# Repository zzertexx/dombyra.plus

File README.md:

# Dombyra Plus
Simple device to teach playing on Dombyra!

## Description
Have you ever wanted to learn playing Dombyra at home?
If yes, then you absolutely looked resources to learn, and what you found was some videos that shows you how they play, while you need to everytime find out which notes is being pressed.

I had exact same problem, so I built this!

This device is solution for it. First hardware addon for Dombyra.

Using bunch of SK6812 LEDs on Dombyra's neck, it will show you which notes need to be pressed right now and after.
By ESP32 and INMP441 mic, it will be controlled by local Website to choose notes and continue showing notes.

## Features
* Wi-Fi website to choose kuis
* 18 LEDs per string with two color mod for Up/Down play
* Battery charge system for autonomuos play
* Comfortable case to play
* Volume spike detector to continue play

## Firmware
* Firmware was written on Arduino IDE
* Currently it has Erkem-Ai
* Needed libraries: FastLED.h, i2s.h(core), WiFi.h(core), WebServer.h(core)

## Attachment
To make sure cases won't move, I added attachment legs for **LED case** and also usage of nylon tape for **microphone case** so you can remove device whenever you want

## How to actually use it?
1) Assemble PCB into Case
2) Use nylon to attach microphone case
3) Compile code into ESP32
4) Place PCBs on dombyra and connect both using **4-pin JST XH2.54** and specialized pins
5) Charge battery and start it
6) Connect to ESP32's Wi-Fi and enter http://192.168.4.1
7) Choose the kui that you wanna learn and enjoy the process!

## Bill of Materials

| Component | Quantity |
|---|---|
| ESP32 DevKit v1 | 1 |
| SK6812 LEDs | 38 |
| INMP441 module | 1 |
| Li-Po Battery + 2 pin header 2mm | 1 |
| USB-C Receptacle only 6 pin | 1 |
| TP4056 module | 1 |
| MT3608 module | 1 |
| M2 screws | 14 |
| M3 screws | 4 |
| 4 pin Connector Sockets - Angled | 1 |
| 4 pin Connector Sockets - Vertical | 1 |
| NTC 10k | 1 |
| Unpolarized capacitors(THT) 10uF & 22uF | 2 each |
| Inductor 4.7uH | 1 |
| Diode | 2 LED and 1 Schottky |
| Resistors | 110k; 15k; 330 x2; 68k; 2.4k; 1k; 0.4; 5k1 x2 |
| 4-pin JST XH2.54 | 1 |
| Nylon Tape | 1 |

## PCB & Schematics
Designed on KiCad 10.0

It consists of 2 PCBs. One on neck for LEDs and second one for Battery, Microphone and MCU. They are connected using 4-pin JST wires for GND, 5V and 2 data channels. 

## Images of cases

## Demo 

https://youtu.be/3Eh5J_6kmjc

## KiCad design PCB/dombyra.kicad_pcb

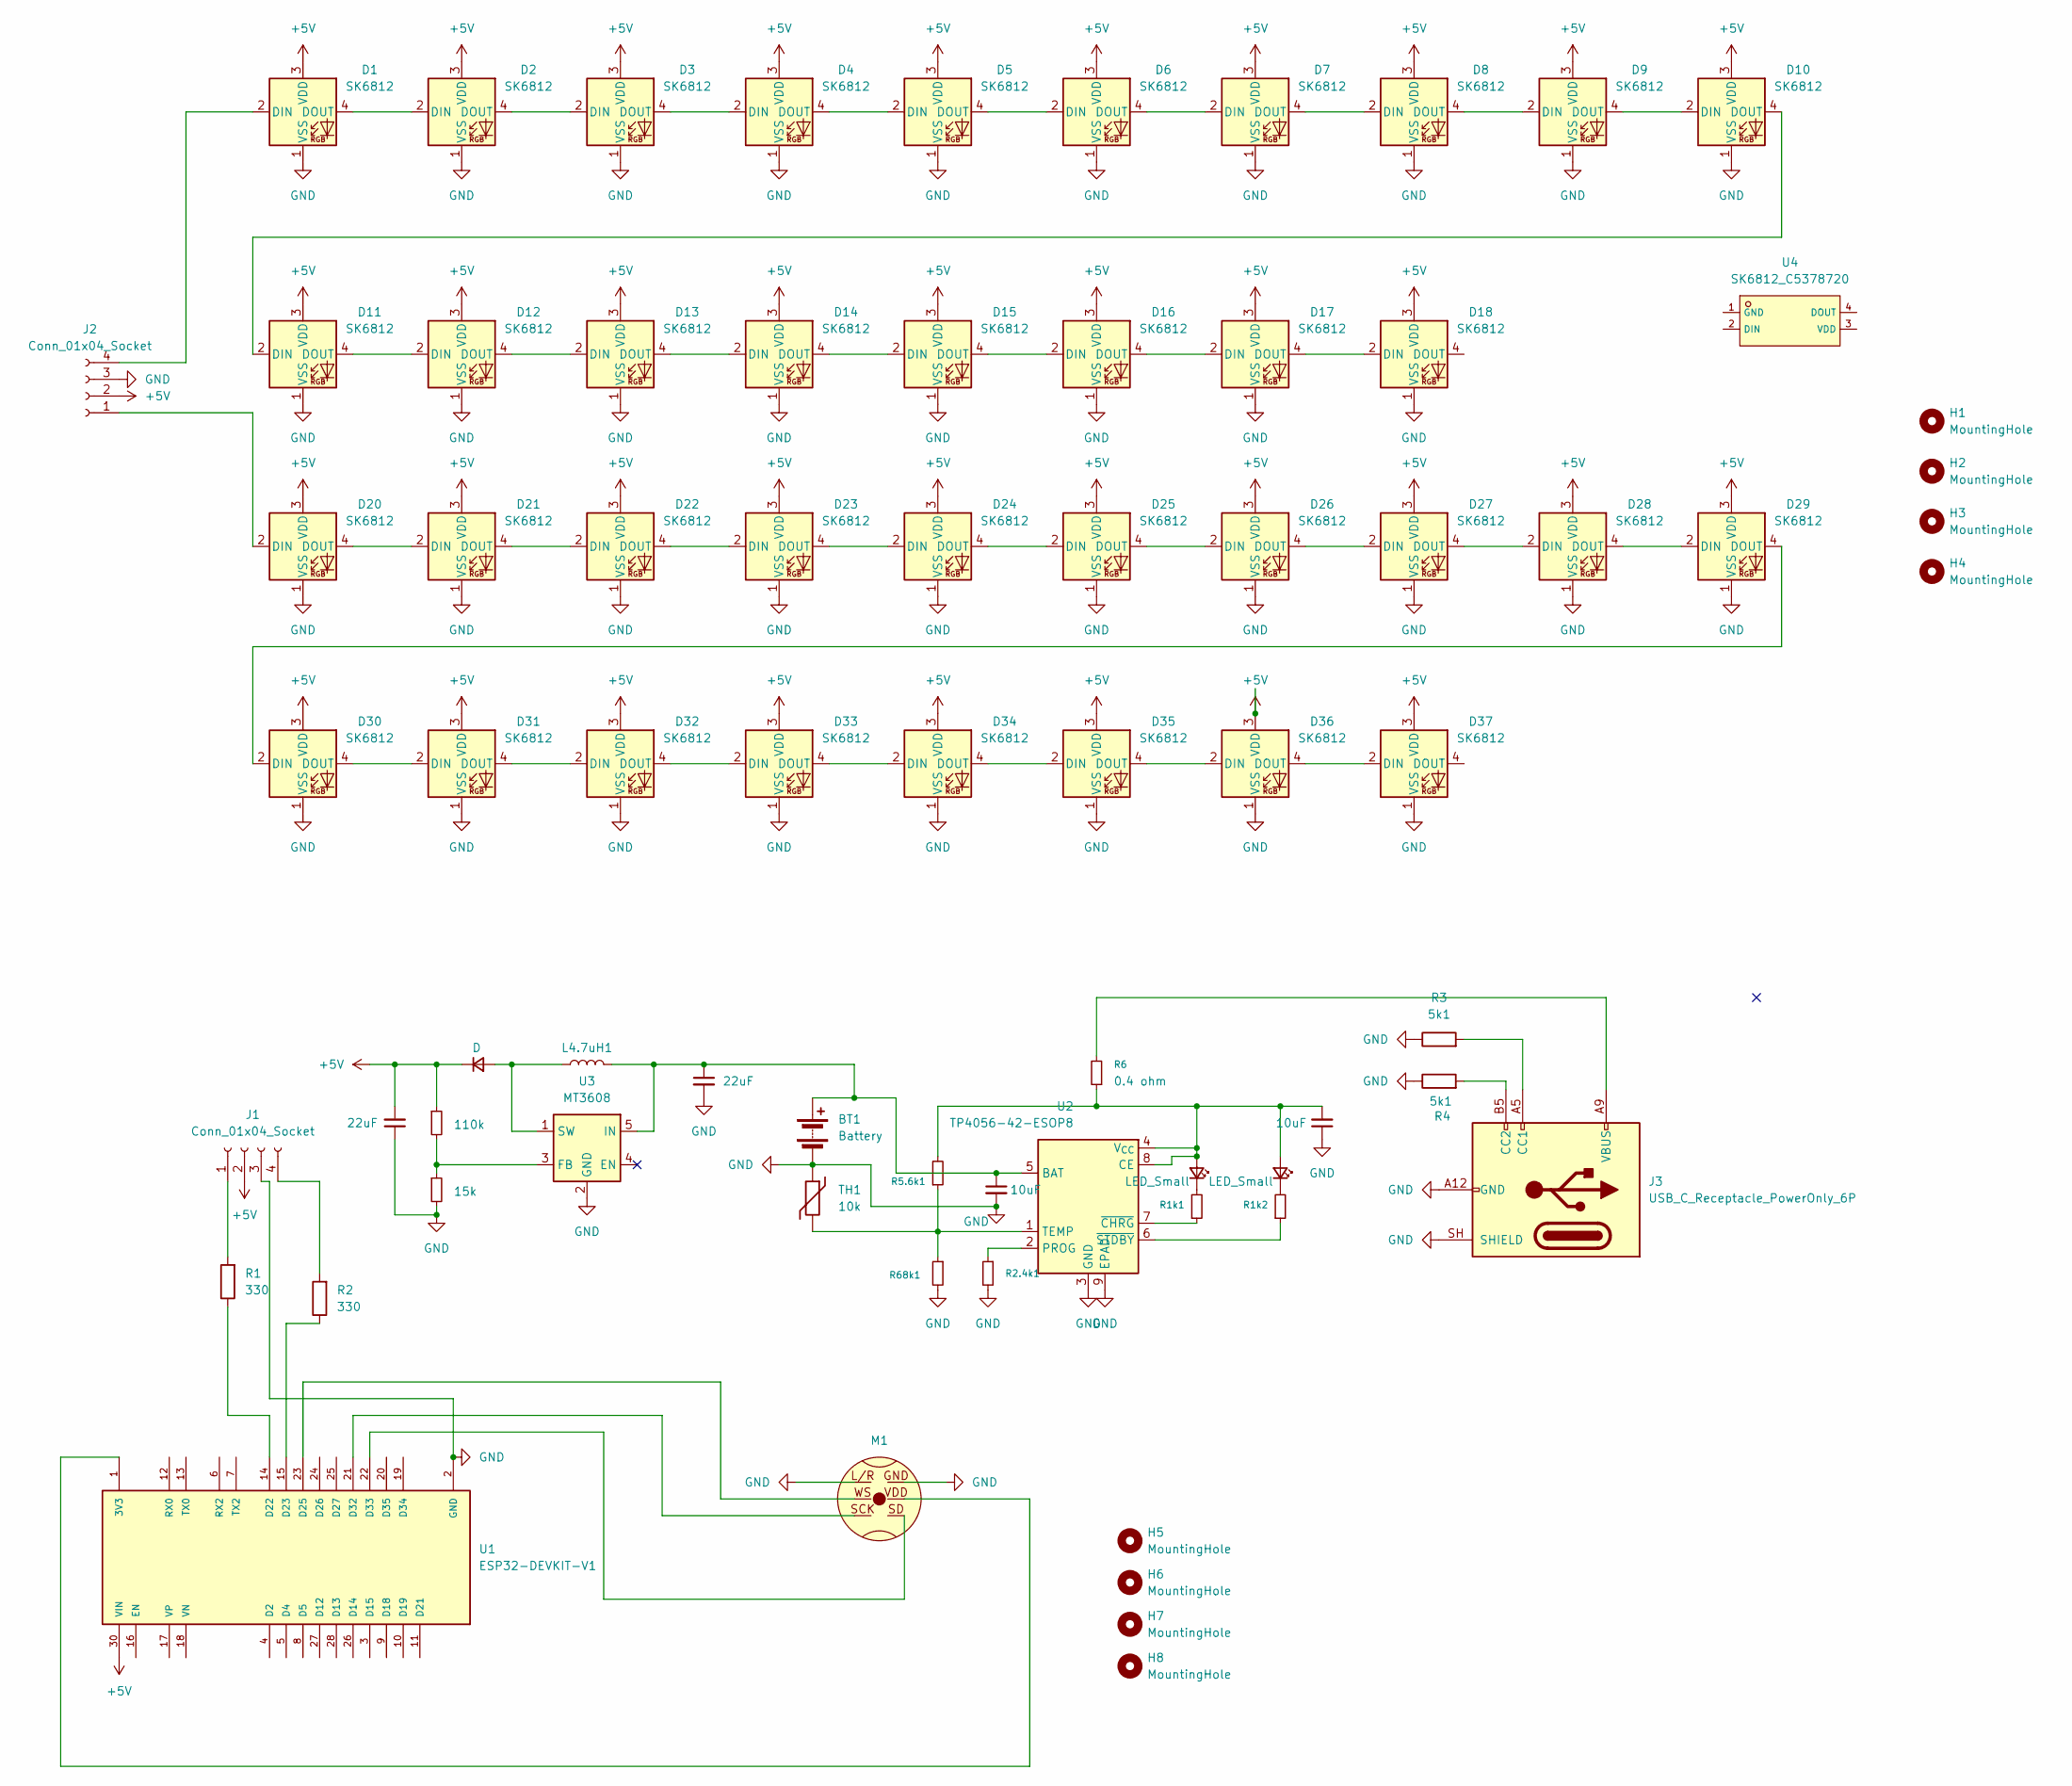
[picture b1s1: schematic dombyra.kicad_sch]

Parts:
BT1: Battery; PinHeader_1x02_P2.54mm_Vertical
C1, C2: 10uF; C_0805_2012Metric
C3, C4: 22uF; C_1206_3216Metric
D1, D2, D3, D4, D5, D6, D7, D8, D9, D10, D11, D12, D13, D14, D15, D16, D17, D18, D20, D21, D22, D23, D24, D25, D26, D27, D28, D29, D30, D31, D32, D33, D34, D35, D36, D37: SK6812; LED_SK6812_PLCC4_5.0x5.0mm_P3.2mm
D39: LED_Small; LED_D3.0mm
D40: LED_Small; LED_D5.0mm
D41: D; SMA_L4.3-W2.6-LS5.2-RD
H1, H2, H3, H4: MountingHole; MountingHole_3.2mm_M3
H5, H6, H7, H8: MountingHole; MountingHole_2.2mm_M2
J1: Conn_01x04_Socket; PinHeader_1x04_P2.54mm_Vertical_SMD_Pin1Left
J2: Conn_01x04_Socket; PinHeader_1x04_P2.54mm_Horizontal
J3: USB_C_Receptacle_PowerOnly_6P; USB_C_Receptacle_GCT_USB4135-GF-A_6P_TopMnt_Horizontal
L4.7uH1: L; L_1812_4532Metric
M1: INMP441
R1, R2: 330; R_0402_1005Metric
R1k1, R1k2: R_Small; R_0805_2012Metric
R2.4k1: R_Small; R_Axial_DIN0204_L3.6mm_D1.6mm_P1.90mm_Vertical
R3, R4: 5k1; R_0603_1608Metric
R5.6k1, R68k1: R_Small; R_0603_1608Metric
R6: 0.4 ohm; R_Axial_DIN0204_L3.6mm_D1.6mm_P1.90mm_Vertical
R9: 15k; R_0402_1005Metric
R10: 110k; R_0603_1608Metric
TH1: 10k; PinHeader_2x01_P2.00mm_Vertical
U1: ESP32-DEVKIT-V1; MODULE_ESP32_DEVKIT_V1; PARTREV N/A
U2: TP4056-42-ESOP8; SOIC-8-1EP_3.9x4.9mm_P1.27mm_EP2.41x3.3mm_ThermalVias
U3: MT3608; SOT-23-6
U4: SK6812_C5378720; LED-SMD_4P-L5.4-W5.0_SK6812; LCSC C5378720

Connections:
+5V: C3.2, D1.3 (VDD), D2.3 (VDD), D3.3 (VDD), D4.3 (VDD), D5.3 (VDD), D6.3 (VDD), D7.3 (VDD), D8.3 (VDD), D9.3 (VDD), D10.3 (VDD), D11.3 (VDD), D12.3 (VDD), D13.3 (VDD), D14.3 (VDD), D15.3 (VDD), D16.3 (VDD), D17.3 (VDD), D18.3 (VDD), D20.3 (VDD), D21.3 (VDD), D22.3 (VDD), D23.3 (VDD), D24.3 (VDD), D25.3 (VDD), D26.3 (VDD), D27.3 (VDD), D28.3 (VDD), D29.3 (VDD), D30.3 (VDD), D31.3 (VDD), D32.3 (VDD), D33.3 (VDD), D34.3 (VDD), D35.3 (VDD), D36.3 (VDD), D37.3 (VDD), D41.1 (K), J1.2, J2.2, R10.1, U1.30 (VIN)
GND: BT1.2 (-), C1.2, C2.1, C3.1, C4.2, D1.1 (VSS), D2.1 (VSS), D3.1 (VSS), D4.1 (VSS), D5.1 (VSS), D6.1 (VSS), D7.1 (VSS), D8.1 (VSS), D9.1 (VSS), D10.1 (VSS), D11.1 (VSS), D12.1 (VSS), D13.1 (VSS), D14.1 (VSS), D15.1 (VSS), D16.1 (VSS), D17.1 (VSS), D18.1 (VSS), D20.1 (VSS), D21.1 (VSS), D22.1 (VSS), D23.1 (VSS), D24.1 (VSS), D25.1 (VSS), D26.1 (VSS), D27.1 (VSS), D28.1 (VSS), D29.1 (VSS), D30.1 (VSS), D31.1 (VSS), D32.1 (VSS), D33.1 (VSS), D34.1 (VSS), D35.1 (VSS), D36.1 (VSS), D37.1 (VSS), J1.3, J2.3, J3.A12 (GND), J3.B12 (GND), J3.SH (SHIELD), M1.GND, M1.L/R, R2.4k1.2, R3.1, R4.1, R9.2, R68k1.2, TH1.1, U1.2 (GND), U1.29 (GND), U2.3 (GND), U2.9 (EPAD), U3.2 (GND)
unnamed: BT1.1 (+), C1.1, C4.1, L4.7uH1.2, U2.5 (BAT), U3.5 (IN)
unnamed: D1.2 (DIN), J2.4
unnamed: D1.4 (DOUT), D2.2 (DIN)
unnamed: D2.4 (DOUT), D3.2 (DIN)
unnamed: D3.4 (DOUT), D4.2 (DIN)
unnamed: D4.4 (DOUT), D5.2 (DIN)
unnamed: D5.4 (DOUT), D6.2 (DIN)
unnamed: D6.4 (DOUT), D7.2 (DIN)
unnamed: D7.4 (DOUT), D8.2 (DIN)
unnamed: D8.4 (DOUT), D9.2 (DIN)
unnamed: D9.4 (DOUT), D10.2 (DIN)
unnamed: D10.4 (DOUT), D11.2 (DIN)
unnamed: D11.4 (DOUT), D12.2 (DIN)
unnamed: D12.4 (DOUT), D13.2 (DIN)
unnamed: D13.4 (DOUT), D14.2 (DIN)
unnamed: D14.4 (DOUT), D15.2 (DIN)
unnamed: D15.4 (DOUT), D16.2 (DIN)
unnamed: D16.4 (DOUT), D17.2 (DIN)
unnamed: D17.4 (DOUT), D18.2 (DIN)
unnamed: D20.2 (DIN), J2.1
unnamed: D20.4 (DOUT), D21.2 (DIN)
unnamed: D21.4 (DOUT), D22.2 (DIN)
unnamed: D22.4 (DOUT), D23.2 (DIN)
unnamed: D23.4 (DOUT), D24.2 (DIN)
unnamed: D24.4 (DOUT), D25.2 (DIN)
unnamed: D25.4 (DOUT), D26.2 (DIN)
unnamed: D26.4 (DOUT), D27.2 (DIN)
unnamed: D27.4 (DOUT), D28.2 (DIN)
unnamed: D28.4 (DOUT), D29.2 (DIN)
unnamed: D29.4 (DOUT), D30.2 (DIN)
unnamed: D30.4 (DOUT), D31.2 (DIN)
unnamed: D31.4 (DOUT), D32.2 (DIN)
unnamed: D32.4 (DOUT), D33.2 (DIN)
unnamed: D33.4 (DOUT), D34.2 (DIN)
unnamed: D34.4 (DOUT), D35.2 (DIN)
unnamed: D35.4 (DOUT), D36.2 (DIN)
unnamed: D36.4 (DOUT), D37.2 (DIN)
unnamed: C2.2, D39.2 (A), D40.2 (A), R5.6k1.2, R6.1, U2.4 (V_{CC}), U2.8 (CE)
unnamed: D39.1 (K), R1k1.2
unnamed: D40.1 (K), R1k2.2
unnamed: D41.2 (A), L4.7uH1.1, U3.1 (SW)
unnamed: J1.1, R1.2
unnamed: J1.4, R2.2
unnamed: J3.A5 (CC1), R3.2
unnamed: J3.B5 (CC2), R4.2
unnamed: J3.A9 (VBUS), J3.B9 (VBUS), R6.2
unnamed: M1.VDD, U1.1 (3V3)
unnamed: R1.1, U1.14 (D22)
unnamed: R2.1, U1.15 (D23)
unnamed: M1.WS, U1.23 (D25)
unnamed: M1.SCK, U1.21 (D32)
unnamed: M1.SD, U1.22 (D33)
unnamed: R2.4k1.1, U2.2 (PROG)
unnamed: R5.6k1.1, R68k1.1, TH1.2, U2.1 (TEMP)
unnamed: R1k1.1, U2.7 (~CHRG)
unnamed: R1k2.1, U2.6 (~STDBY)
unnamed: R9.1, R10.2, U3.3 (FB)

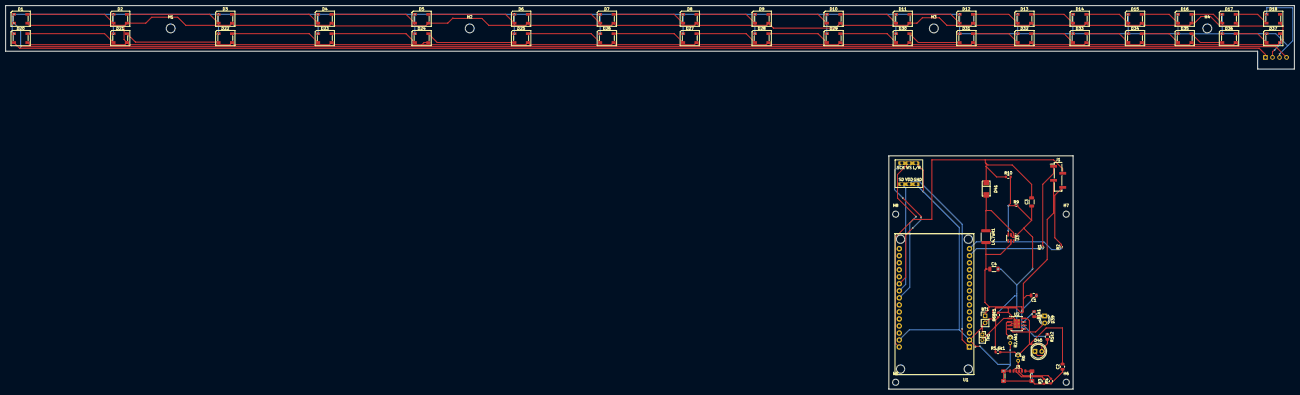
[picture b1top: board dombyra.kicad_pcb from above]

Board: 2 copper layers, 466.1 x 138.7 mm, 73 parts (1 on the bottom side), 59 nets.

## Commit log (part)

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2026-06-06 new zine page
